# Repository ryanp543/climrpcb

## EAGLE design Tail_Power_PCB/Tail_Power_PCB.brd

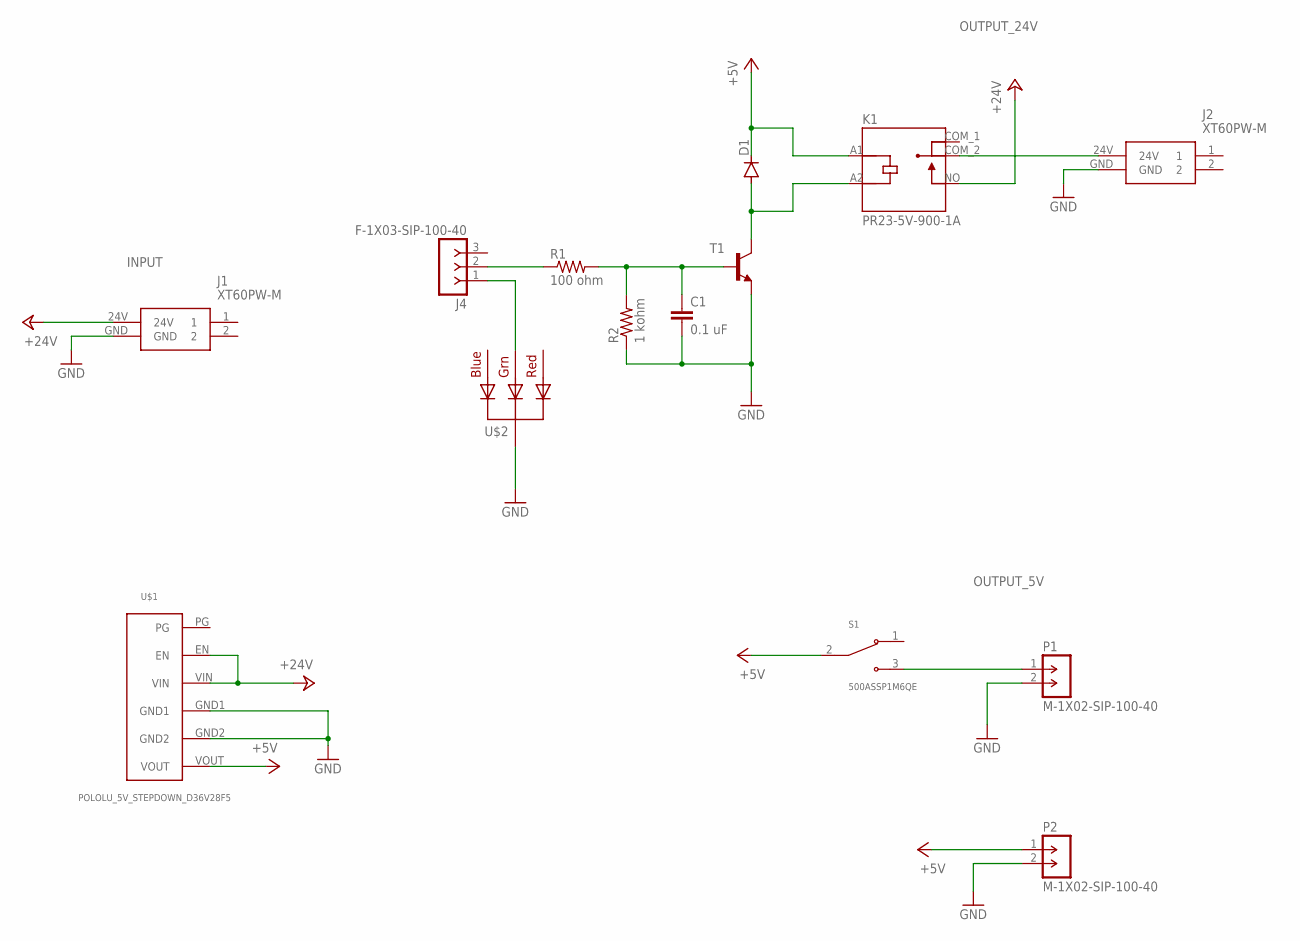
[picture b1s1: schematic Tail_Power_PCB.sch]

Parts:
C1: 0.1 uF; C10B4
D1: DIODE-DO41-7.6; DO41-7.6
J1, J2: XT60PW-M; XT60PWM
J4: F-1X03-SIP-100-40; SIP-100-03-40
K1: PR23-5V-900-1A; RELAY_PR23-5V-900-1A
P1, P2: M-1X02-SIP-100-40; SIP-100-02-40
R1: 100 ohm; 0204/7
R2: 1 kohm; 0204/7
S1: 500ASSP1M6QE; SW_500ASSP1M6QE
T1: -NPN-TO92; TO92
U$1: POLOLU_5V_STEPDOWN_D36V28F5; MODULE_POLOLU_3782
U$2: KINGBRIGHT_LED; LEDWP154A4SUREQBFZGW

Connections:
+5V: D1.C, K1.A1 (COIL1), P2.1, S1.2 (COM), U$1.VOUT
+24V: J1.24V, K1.NO, U$1.EN, U$1.VIN
GND: C1.2, J1.GND, J2.GND, P1.2, P2.2, R2.1, T1.1 (E), U$1.GND1, U$1.GND2, U$2.GND
unnamed: P1.1, S1.3 (NO)
unnamed: J2.24V, K1.COM_2 (COM2)
unnamed: C1.1, R1.2, R2.2, T1.2 (B)
unnamed: J4.2, R1.1
unnamed: J4.1, U$2.GRN (GREEN)
unnamed: D1.A, K1.A2 (COIL2), T1.3 (C)

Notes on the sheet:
INPUT
OUTPUT_24V
OUTPUT_5V

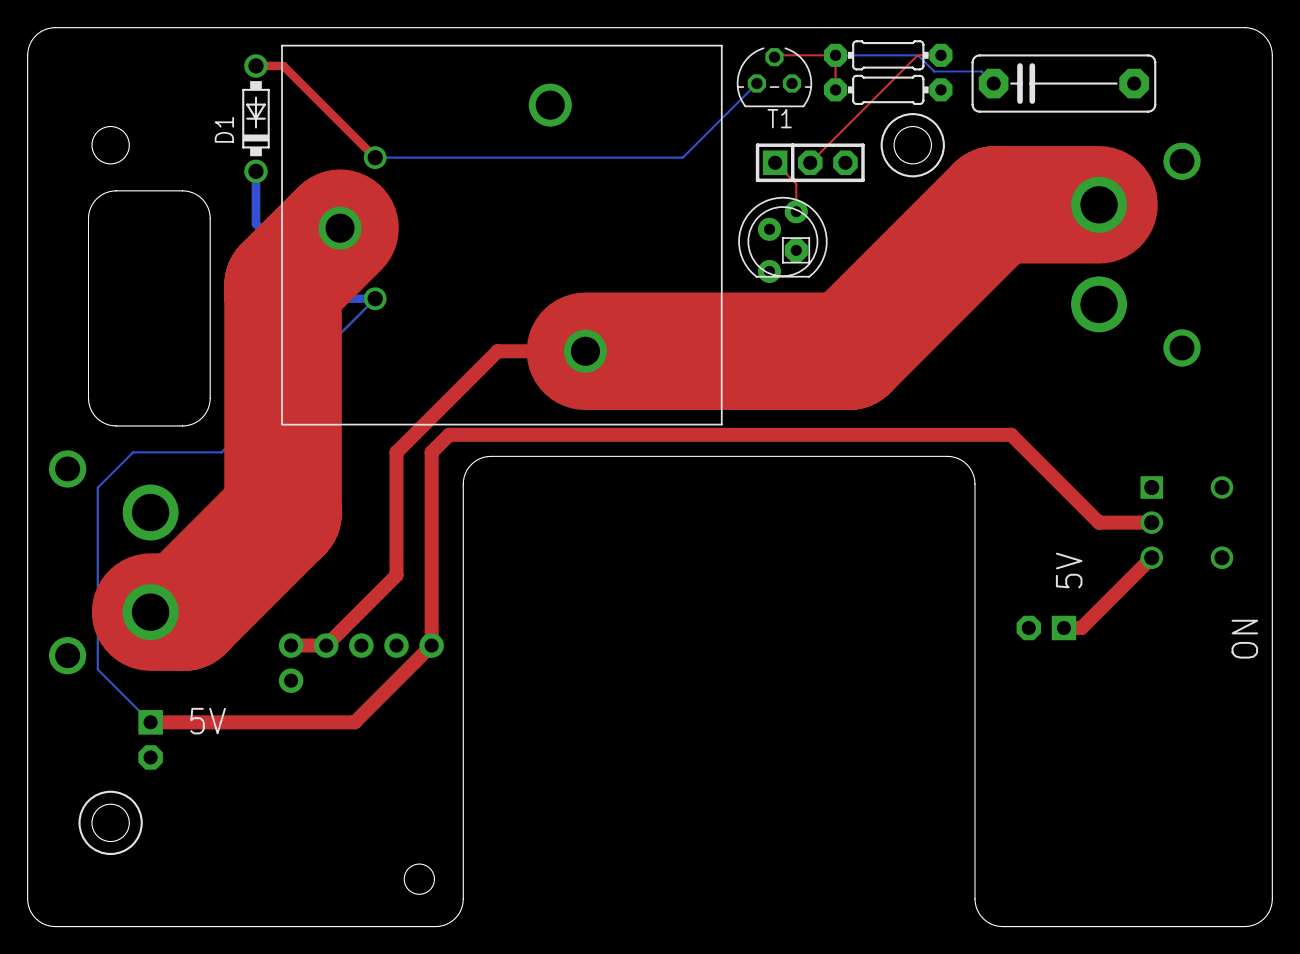
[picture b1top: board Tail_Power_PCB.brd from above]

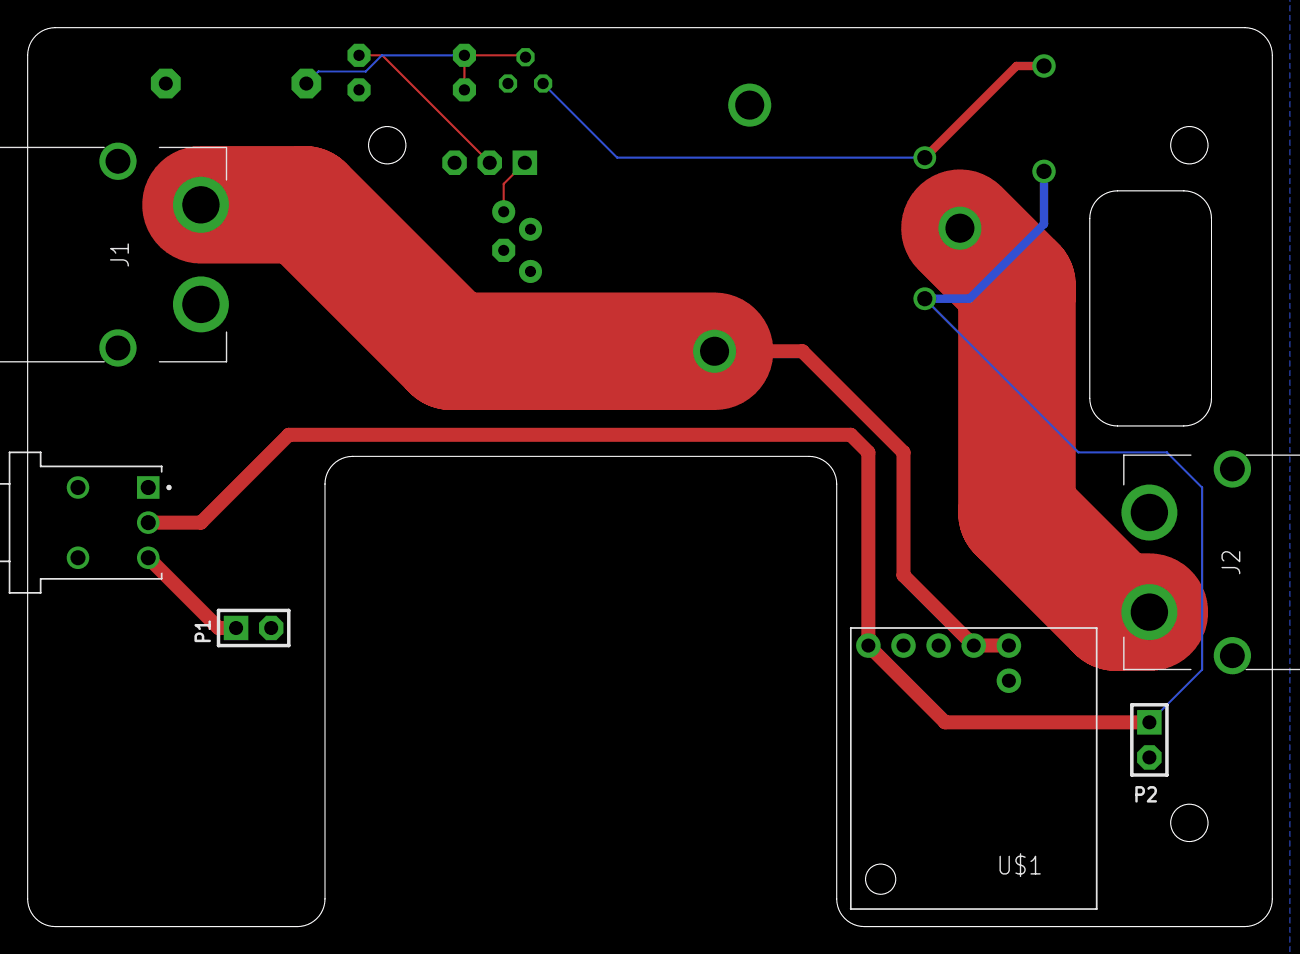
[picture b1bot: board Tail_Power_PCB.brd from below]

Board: 2 copper layers, 90.0 x 65.0 mm, 14 parts (6 on the bottom side), 9 nets.

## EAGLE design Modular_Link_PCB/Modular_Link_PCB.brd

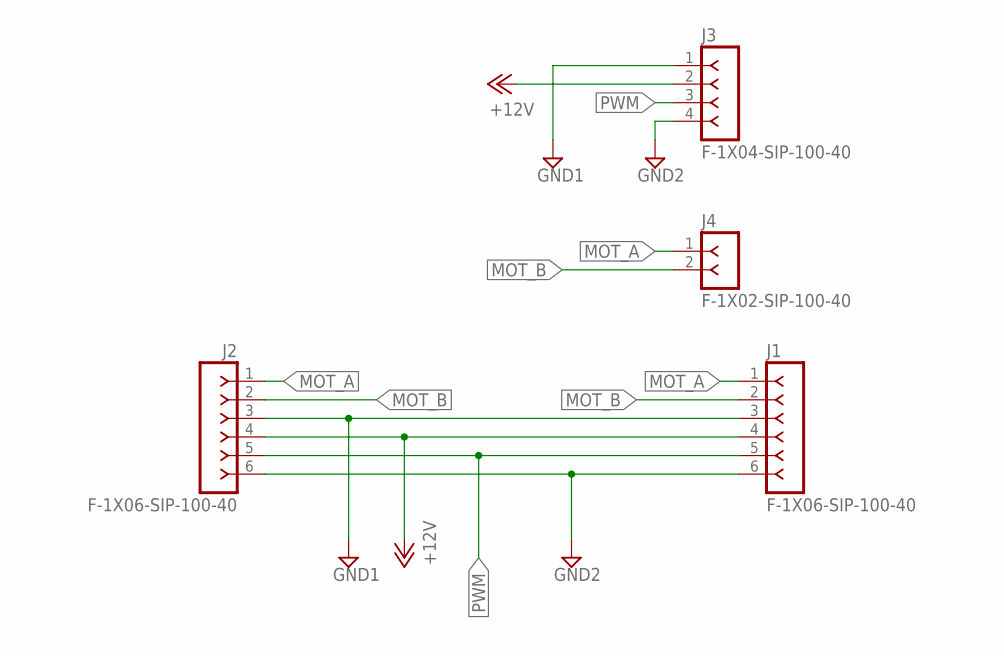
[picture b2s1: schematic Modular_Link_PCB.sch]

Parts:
J1, J2: F-1X06-SIP-100-40; SIP-100-06-40
J3: F-1X04-SIP-100-40; SIP-100-04-40
J4: F-1X02-SIP-100-40; SIP-100-02-40

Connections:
+12V: J1.4, J2.4, J3.2
GND1: J1.3, J2.3, J3.1
GND2: J1.6, J2.6, J3.4
MOT_A: J1.1, J2.1, J4.1
MOT_B: J1.2, J2.2, J4.2
PWM: J1.5, J2.5, J3.3

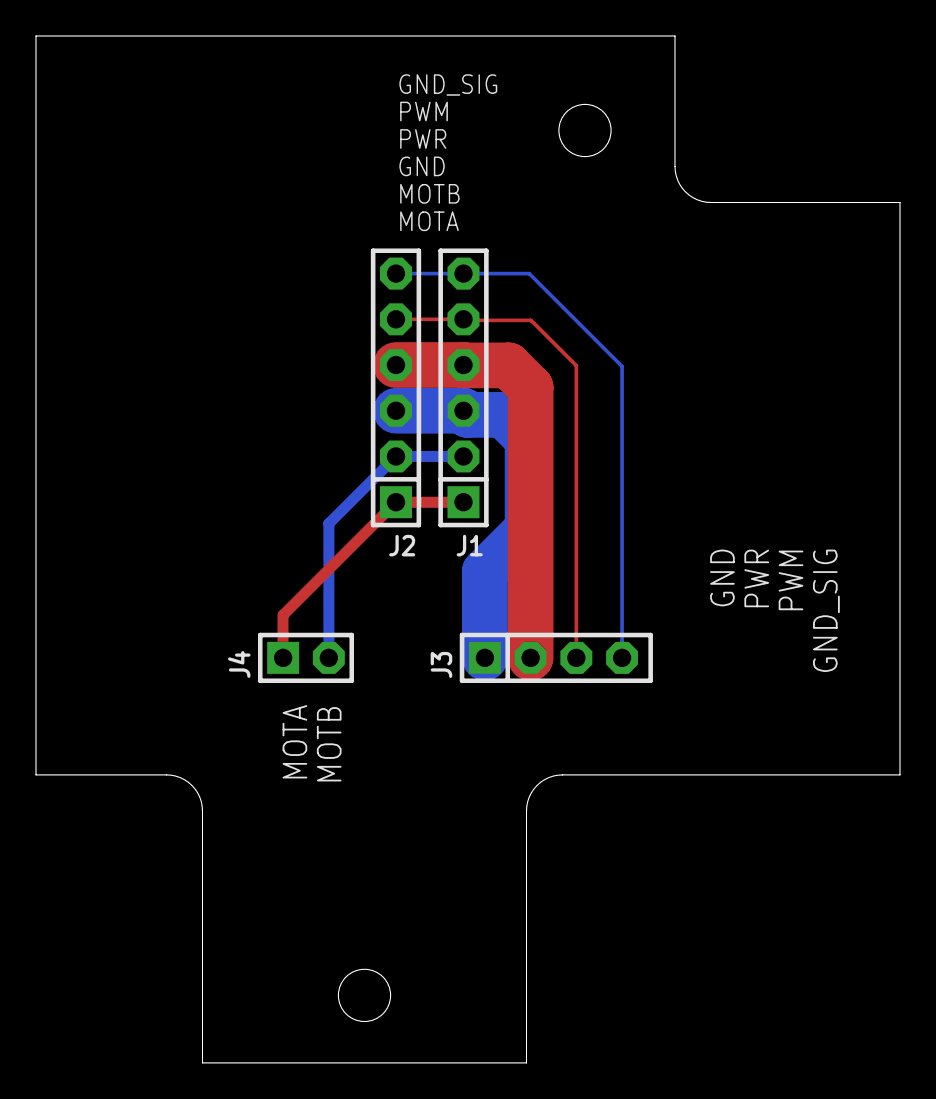
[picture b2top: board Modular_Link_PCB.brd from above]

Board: 2 copper layers, 48.0 x 57.0 mm, 4 parts (0 on the bottom side), 6 nets.

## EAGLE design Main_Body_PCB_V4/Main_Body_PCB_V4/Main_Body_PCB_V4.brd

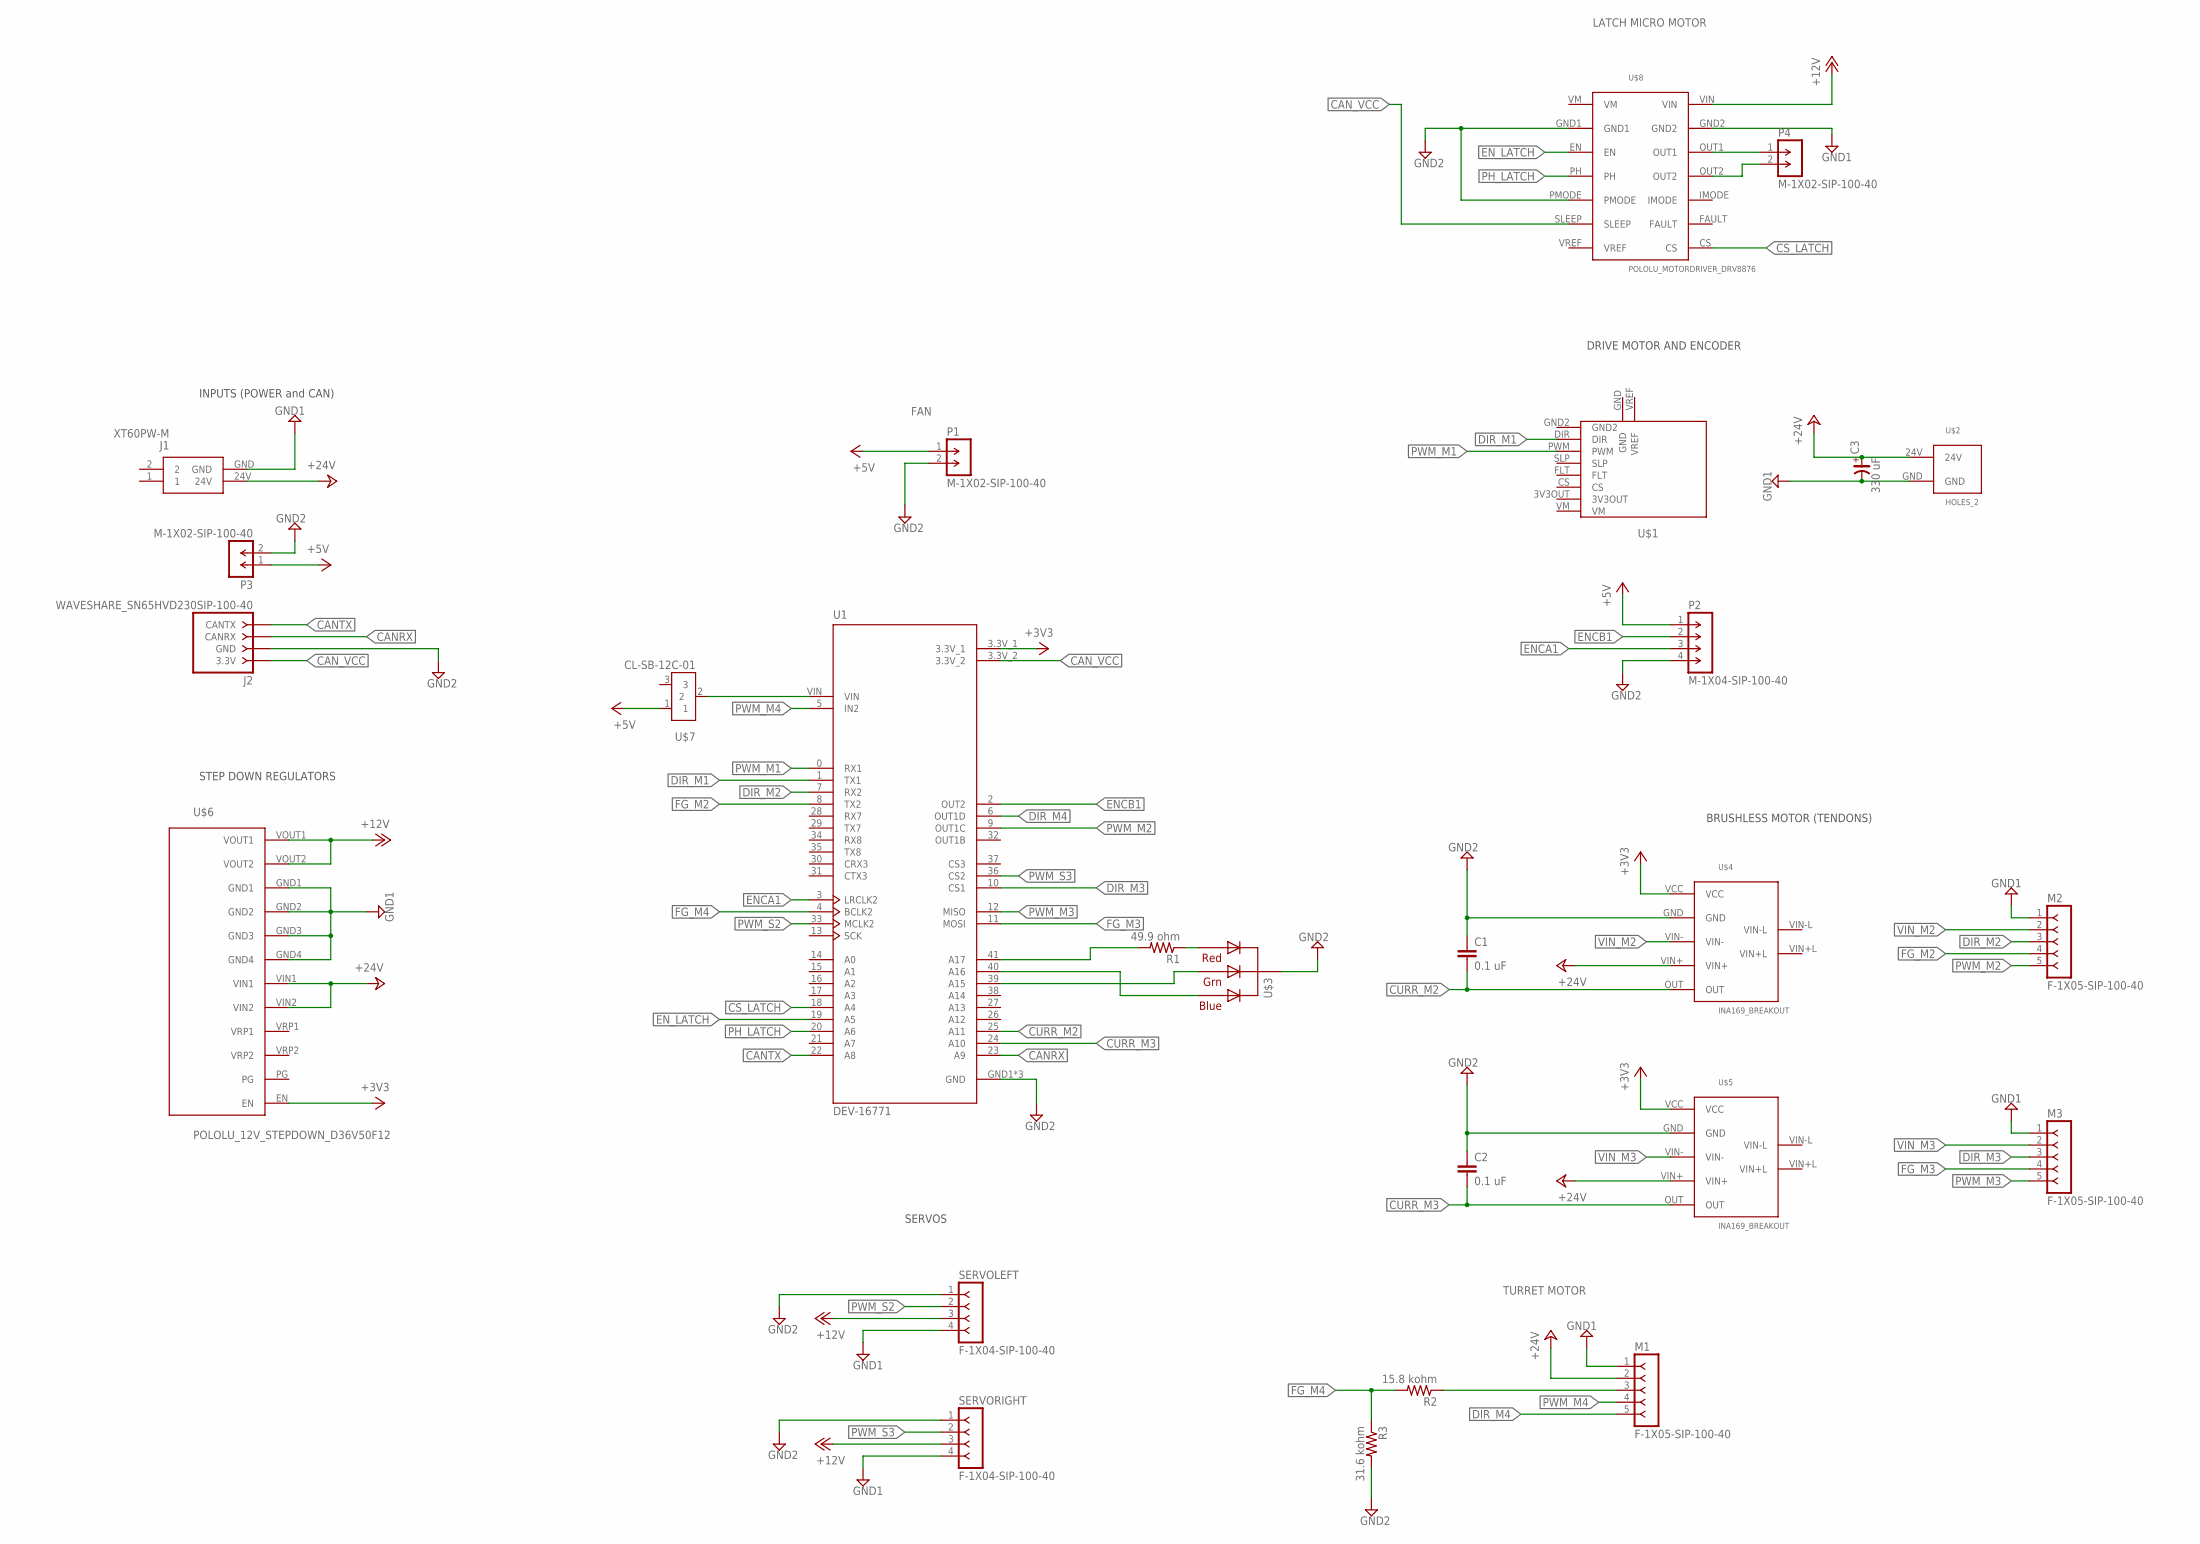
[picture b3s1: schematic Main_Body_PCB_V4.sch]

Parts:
C1, C2: 0.1 uF; C10B4
C3: 330 uF; CE-050X100
J1: XT60PW-M; XT60PWM
J2: WAVESHARE_SN65HVD230SIP-100-40; SIP-100-04-40_PPTC041LGBN-RC
M1, M2, M3: F-1X05-SIP-100-40; SIP-100-05-40
P1, P3, P4: M-1X02-SIP-100-40; SIP-100-02-40
P2: M-1X04-SIP-100-40; SIP-100-04-40
R1: 49.9 ohm; 0204/7
R2: 15.8 kohm; 0204/7
R3: 31.6 kohm; 0204/7
SERVOLEFT: F-1X04-SIP-100-40; SIP-100-04-40
SERVORIGHT: F-1X04-SIP-100-40; SIP-100-04-40
U1: DEV-16771; MODULE_DEV-16771
U$1: POLOLU_MOTORDRIVER_18V25_MOD; MODULE_POLOLU_2992/2994_MOD
U$2: HOLES_2
U$3: KINGBRIGHT_LED; LEDWP154A4SUREQBFZGW
U$4, U$5: INA169_BREAKOUT; MODULE_INA169_BREAKOUT
U$6: POLOLU_12V_STEPDOWN_D36V50F12; MODULE_POLOLU_4093
U$7: CL-SB-12C-01
U$8: POLOLU_MOTORDRIVER_DRV8876; MODULE_POLOLU_4036

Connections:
+3V3: U1.3.3V_1, U$4.VCC, U$5.VCC, U$6.EN
+5V: P1.1, P2.1, P3.1, U$7.1
+12V: SERVOLEFT.3, SERVORIGHT.3, U$6.VOUT1, U$6.VOUT2, U$8.VIN
+24V: C3.+, J1.24V, M1.2, U$2.24V, U$4.VIN+, U$5.VIN+, U$6.VIN1, U$6.VIN2
CANRX: J2.CANRX, U1.23 (A9)
CANTX: J2.CANTX, U1.22 (A8)
CAN_VCC: J2.3.3V, U1.3.3V_2, U$8.SLEEP
CS_LATCH: U1.18 (A4), U$8.CS
CURR_M2: C1.2, U1.25 (A11), U$4.OUT
CURR_M3: C2.2, U1.24 (A10), U$5.OUT
DIR_M1: U1.1 (TX1), U$1.DIR
DIR_M2: M2.3, U1.7 (RX2)
DIR_M3: M3.3, U1.10 (CS1)
DIR_M4: M1.5, U1.6 (OUT1D)
ENCA1: P2.3, U1.3 (LRCLK2)
ENCB1: P2.2, U1.2 (OUT2)
EN_LATCH: U1.19 (A5), U$8.EN
FG_M2: M2.4, U1.8 (TX2)
FG_M3: M3.4, U1.11 (MOSI)
FG_M4: R2.2, R3.1, U1.4 (BCLK2)
GND1: C3.-, J1.GND, M1.1, M2.1, M3.1, SERVOLEFT.4, SERVORIGHT.4, U$2.GND, U$6.GND1, U$6.GND2, U$6.GND3, U$6.GND4, U$8.GND2
GND2: C1.1, C2.1, J2.GND, P1.2, P2.4, P3.2, R3.2, SERVOLEFT.1, SERVORIGHT.1, U1.GND1 (GND), U1.GND2 (GND), U1.GND3 (GND), U$3.GND, U$4.GND, U$5.GND, U$8.GND1, U$8.PMODE
unnamed: U1.VIN, U$7.2
unnamed: U1.40 (A16), U$3.BLU (BLUE)
unnamed: R1.1, U$3.RED
unnamed: M1.3, R2.1
unnamed: R1.2, U1.41 (A17)
unnamed: U1.39 (A15), U$3.GRN (GREEN)
unnamed: P4.1, U$8.OUT1
unnamed: P4.2, U$8.OUT2
PH_LATCH: U1.20 (A6), U$8.PH
PWM_M1: U1.0 (RX1), U$1.PWM
PWM_M2: M2.5, U1.9 (OUT1C)
PWM_M3: M3.5, U1.12 (MISO)
PWM_M4: M1.4, U1.5 (IN2)
PWM_S2: SERVOLEFT.2, U1.33 (MCLK2)
PWM_S3: SERVORIGHT.2, U1.36 (CS2)
VIN_M2: M2.2, U$4.VIN-
VIN_M3: M3.2, U$5.VIN-

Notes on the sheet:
INPUTS (POWER and CAN)
SERVOS
STEP DOWN REGULATORS
BRUSHLESS MOTOR (TENDONS)
DRIVE MOTOR AND ENCODER
TURRET MOTOR
FAN
LATCH MICRO MOTOR

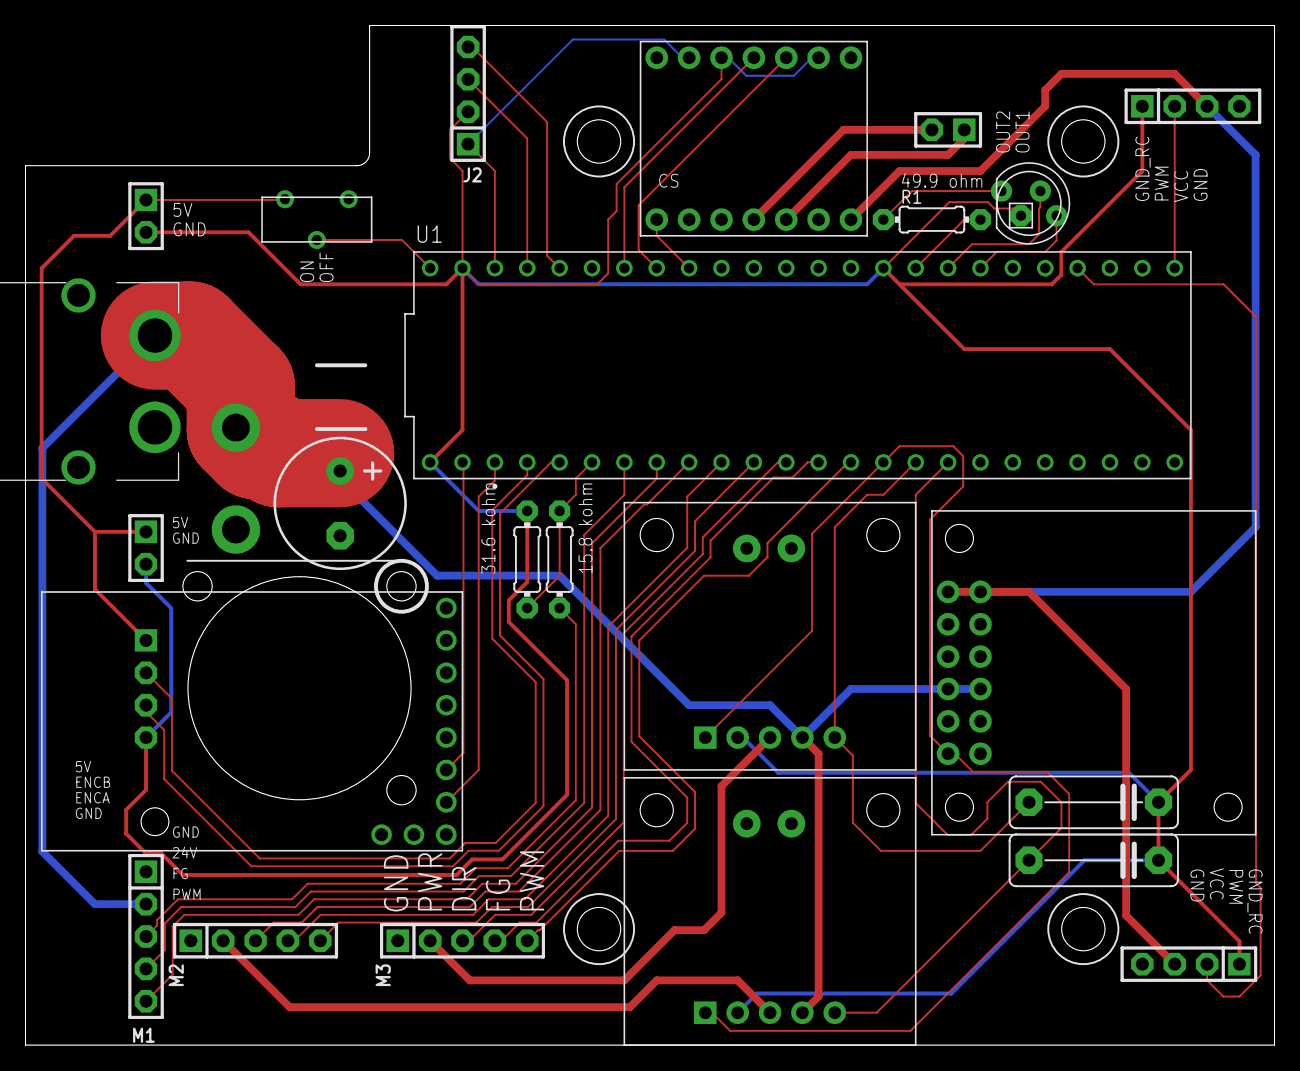
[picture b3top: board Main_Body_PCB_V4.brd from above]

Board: 2 copper layers, 98.0 x 80.0 mm, 26 parts (1 on the bottom side), 39 nets.

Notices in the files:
parts and their libraries:
con-headers-jp: Copyright (C) 2008, Bob Starr
rc-master: Copyright (C) 2007, Bob Starr
